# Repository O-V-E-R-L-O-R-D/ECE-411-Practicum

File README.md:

# ECE-411-Practicum Project

## Color Sensor State Diagram

## Bootload and Programming
**Library for Bootload Raw Chip:** https://github.com/MCUdude/
MiniCore

**1.) Add "https://mcudude.github.io/MiniCore/package_MCUdude_MiniCore_index.json" to Arduino IDE's "Additional boards manager URL's"**

---
**2.) Open example project "AruinoISP"**

---
**3.) Program Arduino Uno for programming by clicking "Upload button" with the Aruino Uno board selected. Also in the "Tools" tab select "ArduinoISP" for programmer** 

---
**4.) Make connections from Aruduino Uno to PCB. On PCB, move bottem left switch to Program Mode (PRGM) by sliding the switch to the left**

| Arduino Uno |->| PCB |
|-------------|--|-----|
|5V           |->|VCC  | 
|GND          |->|GND  |
|13           |->|CLK  |
|12           |->|MISO |
|11           |->|MOSI |
|10           |->|Reset|

---
**5.) Bootload ATmega328 by opening "Tools tab and clicking "Burn Bootloader" after changing the settings to the ones seen below.**  
Board: "ATmega328"
BOD: 2.7V  
Clock: "External 8MHz"  
EEPROM: "EEPROM not retained"  (Not Necessary, For Clearing Color Calibration data)  
Variant: "328P/32PA"  
Programmer: "Arduino as ISP"  

---
**6.) Switch to RGB_Sensor_Project.ino ("ECE-411-Practicum/RGB_sensor_project/RGB_sensor_project.ino"). Open Tools tab and make sure "Programmer" is set to "Arduino as ISP".With the ATmega328 board selected, open the "Sketch" tab and click "Upload Using Programmer"**

---
**7.) Unplug Programming connectings to PCB and flip the bottom right switch on the PCB to "NORM" mode. Make sure the PCB is getting power from the batter to the PCB. If this is the firt time programming the device the OLED should show that it's entering calibration mode.**  

**NOTE:** After first bootload you don't need to do it again for that chip. If you want to upload a new Schetch to the chip you only need to flip bottem left switch to PRGM, make the right programming connections, and then go straight to step 6.

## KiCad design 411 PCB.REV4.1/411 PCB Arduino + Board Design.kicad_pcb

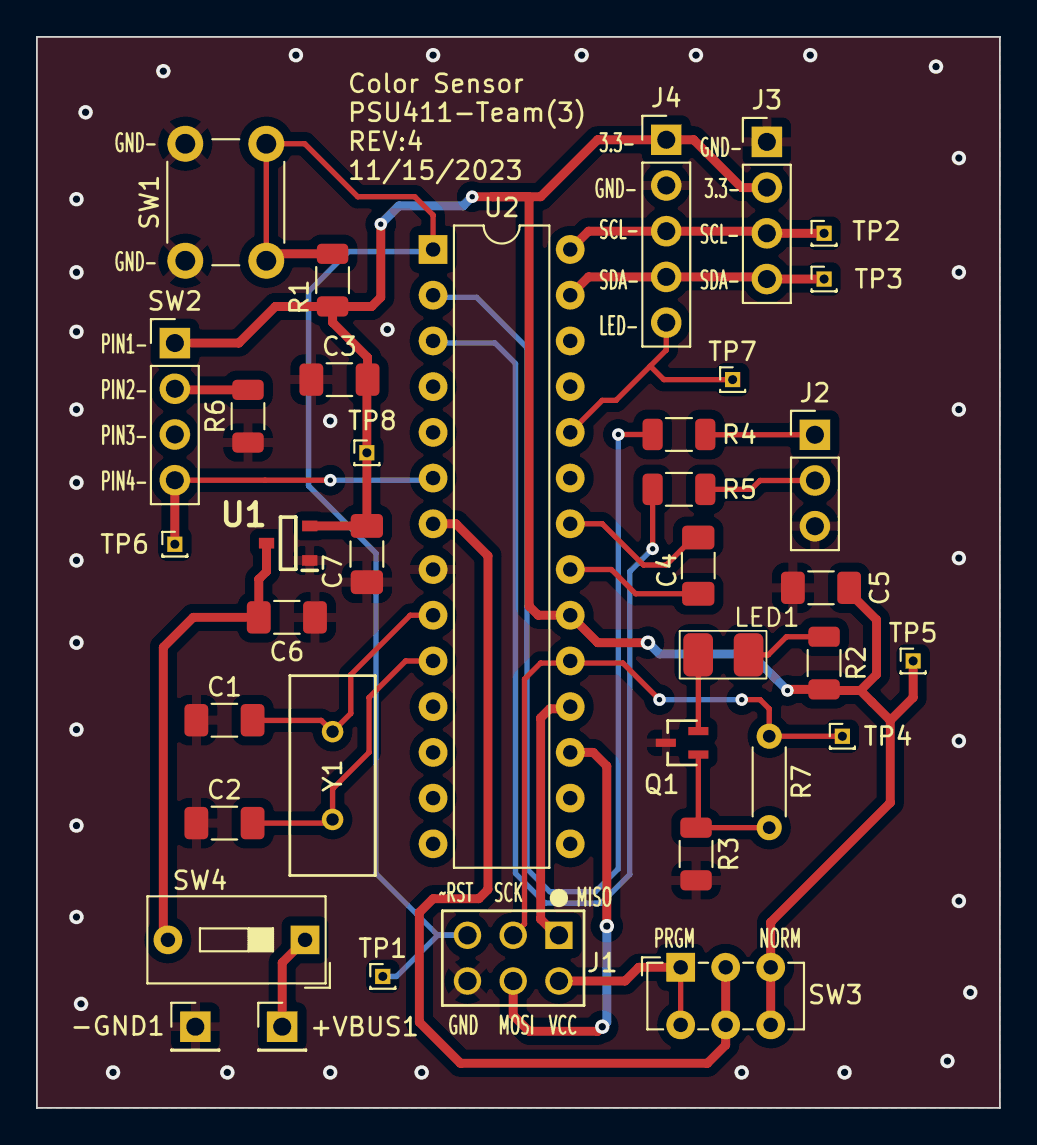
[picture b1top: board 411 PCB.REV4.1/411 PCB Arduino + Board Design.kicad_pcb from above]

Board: 2 copper layers, 53.5 x 59.5 mm, 37 parts (0 on the bottom side), 26 nets.

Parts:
+VBUS1: Conn_01x01_Pin; PinHeader_1x01_P2.54mm_Vertical
-GND1: Conn_01x01_Pin; PinHeader_1x01_P2.54mm_Vertical
C1, C2: 30p; C_1206_3216Metric_Pad1.33x1.80mm_HandSolder
C3, C4, C5: 100n; C_1206_3216Metric_Pad1.33x1.80mm_HandSolder
C6, C7: 1uF; C_1206_3216Metric_Pad1.33x1.80mm_HandSolder
J1: ICSP CONN; CONN_PH2-06-UA_ADM
J2: PinHeader_1x03_P2.54mm_Vertical
J3: Conn_01x04; PinHeader_1x04_P2.54mm_Vertical
J4: Conn_01x05_Pin; PinHeader_1x05_P2.54mm_Vertical
LED1: Blue LED (100mA Max); LTST-B680
Q1: Q_NMOS_GDS; SOIC_D8LW-13_DIO
R1, R3, R6: 10k; R_1206_3216Metric
R2, R4, R5: 1k; R_1206_3216Metric
R7: 0 Ohm; R_Axial_DIN0204_L3.6mm_D1.6mm_P5.08mm_Horizontal
SW1: SW_SPST; SW_PUSH_6mm
SW2: SW_MEC_5E; PinHeader_1x04_P2.54mm_Vertical
SW3: SW_SPDT; SW_E-Switch_EG1271_SPDT_123
SW4: SW_DPST_x2; SW_DIP_SPSTx01_Slide_9.78x4.72mm_W7.62mm_P2.54mm
TP1, TP2, TP3, TP4, TP5, TP6, TP7, TP8: TestPoint; PinHeader_1x01_P1.00mm_Vertical
U1: SOT96P240X120-3N
U2: ATmega328P-P; DIP-28_W7.62mm
Y1: 8 MHz; ATS08A-E_CTS

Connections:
+3.3V: C3.2, C5.2, C7.1, J3.2, J4.1, R1.1, R2.1, SW2.1, SW3.3 (C), TP5.1, TP8.1, U1.2 (VOUT), U2.20 (AVCC)
+5V: J1.2 (VCC), SW3.1 (A)
/LED_EN: J4.5, TP7.1, U2.24 ((ADC1)PC1)
/SDA+: J3.4, J4.4, TP3.1, U2.27 (SDA+)
/SDA-: J3.3, J4.3, TP2.1, U2.28 (SDA-)
GND: -GND1.1, C1.1, C2.1, C3.1, C5.1, C6.2, C7.2, J1.6 (GND), J2.3, J3.1, J4.2, Q1.3 (S), R3.2, R6.1, SW1.1 (A), U1.1 (GND), U2.8 (GND)
unnamed: +VBUS1.1, SW4.1 (A)
unnamed: C4.2, U2.22 (GND)
unnamed: J1.1 (MISO), U2.18 ((MISO)PB4)
unnamed: J1.4 (MOSI), U2.17 ((MOSI)PB3)
unnamed: J1.3 (SCK), R7.2, TP4.1, U2.19 ((SCK)PB5)
unnamed: J1.5 (~RST), R1.2, SW1.2 (B), TP1.1, U2.1 (~RESET/PC6)
unnamed: J2.1, R4.2
unnamed: J2.2, R5.2
unnamed: LED1.2 (A), R2.2
unnamed: LED1.1 (K), Q1.2 (D)
unnamed: Q1.1 (G), R3.1, R7.1
unnamed: R6.2, SW2.2
unnamed: SW2.4 (A), TP6.1, U2.6 ((T0)PD4)
unnamed: C6.1, SW4.2 (B), U1.3 (VIN)
unnamed: R4.1, U2.2 ((RXD)PD0)
unnamed: R5.1, U2.3 ((TXD)PD1)
unnamed: C4.1, U2.21 (AREF)
unnamed: C1.2, U2.9 (XTAL+), Y1.2
unnamed: C2.2, U2.10 (XTAL-), Y1.1
VCC: SW3.2 (B), U2.7 (VCC)

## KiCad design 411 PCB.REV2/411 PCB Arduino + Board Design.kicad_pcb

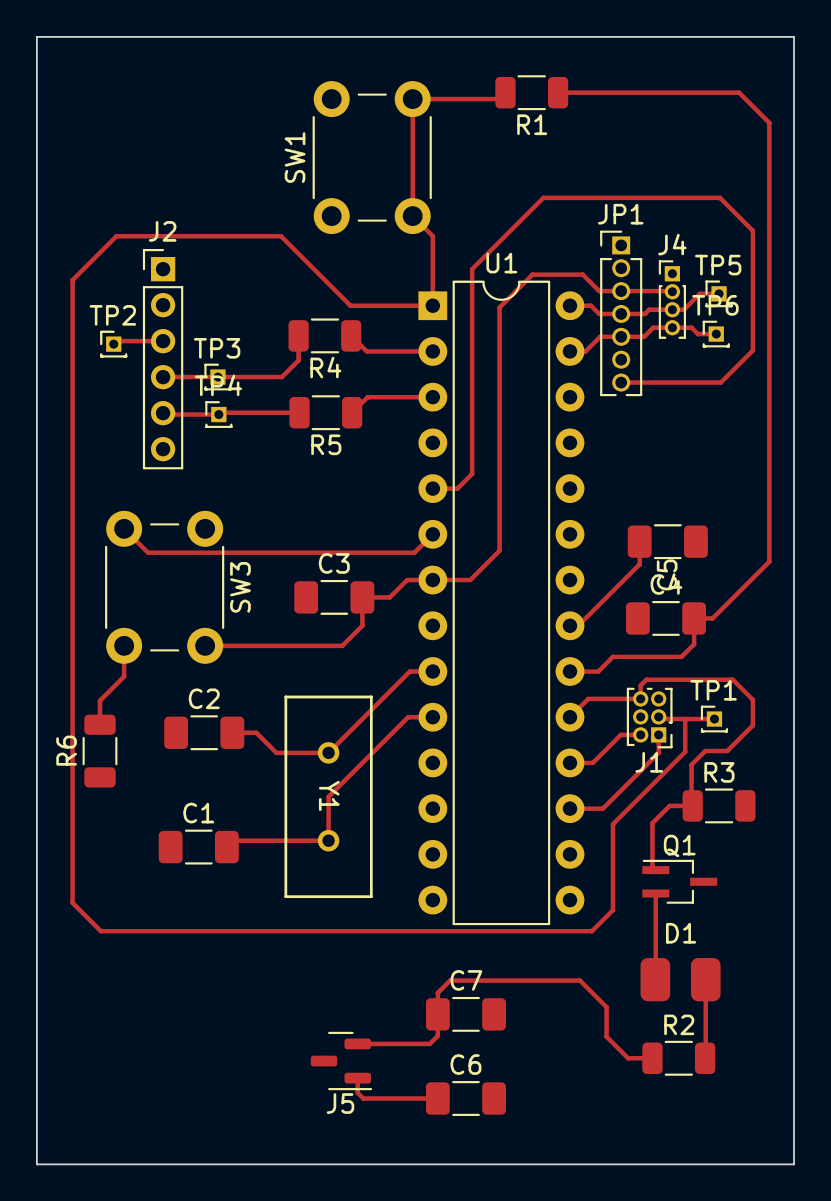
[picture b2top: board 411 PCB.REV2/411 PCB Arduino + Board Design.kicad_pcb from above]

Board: 2 copper layers, 42.1 x 62.6 mm, 30 parts (0 on the bottom side), 22 nets.

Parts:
C1, C2: 10p; C_1206_3216Metric_Pad1.33x1.80mm_HandSolder
C3, C4, C5: 100n; C_1206_3216Metric_Pad1.33x1.80mm_HandSolder
C6, C7: 1uF; C_1206_3216Metric_Pad1.33x1.80mm_HandSolder
D1: LED (100mA Max); LED_0805_2012Metric_Pad1.15x1.40mm_HandSolder
J1: ICSP CONN; PinHeader_2x03_P1.00mm_Vertical
J2: Conn_01x06_MountingPin; PinHeader_1x06_P2.00mm_Vertical
J4: Conn_01x04; PinHeader_1x04_P1.00mm_Vertical
J5: SOT-23
JP1: HEADER-1X770MIL; PinHeader_1x07_P1.27mm_Vertical
Q1: Q_NMOS_GDS; SOT-323_SC-70_Handsoldering
R1, R3, R6: 10k; R_1206_3216Metric
R2, R4, R5: 1k; R_1206_3216Metric
SW1: SW_SPST; SW_PUSH_6mm
SW3: SW_MEC_5E; SW_PUSH_6mm
TP1, TP2, TP3, TP4, TP5, TP6: TestPoint; PinHeader_1x01_P1.00mm_Vertical
U1: ATmega328P-P; DIP-28_W7.62mm
Y1: 8 MHz; ATS08A-E_CTS

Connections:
+3.3V: C3.2, C4.2, C7.1, J4.2, J5.2 (VOUT), JP1.3, R1.1, R2.1, SW3.1, U1.7 (VCC), U1.20 (AVCC)
+VDC: C6.1, J5.1 (VIN)
/LED_EN: JP1.7, U1.5 ((INT1)PD3)
/SCL_3.3V: J4.3, JP1.4, TP5.1, U1.28 ((ADC5/SCL)PC5)
/SDA_3.3V: J4.4, JP1.5, TP6.1, U1.27 ((ADC4/SDA)PC4)
GND: C1.1, C2.1, C3.1, C4.1, C5.1, C6.2, C7.2, J1.6 (GND), J2.1, J4.1, J5.3 (GND), JP1.2, Q1.3 (S), R3.2, R6.1, SW1.1 (A), U1.8 (GND), U1.22 (GND)
unnamed: D1.2 (A), R2.2
unnamed: D1.1 (K), Q1.2 (D)
unnamed: J1.1 (MISO), U1.18 ((MISO)PB4)
unnamed: J1.4 (MOSI), U1.17 ((MOSI)PB3)
unnamed: J1.3 (SCK), Q1.1 (G), R3.1, U1.19 ((SCK)PB5)
unnamed: J1.5 (~RST), R1.2, SW1.2 (B), TP1.1, U1.1 (~RESET/PC6)
unnamed: J2.3, TP2.1
unnamed: J2.4, R4.2, TP3.1
unnamed: J2.5, R5.2, TP4.1
unnamed: R6.2, SW3.2
unnamed: SW3.4 (A), U1.6 ((T0)PD4)
unnamed: R4.1, U1.2 ((RXD)PD0)
unnamed: R5.1, U1.3 ((TXD)PD1)
unnamed: C5.2, U1.21 (AREF)
unnamed: C2.2, U1.9 (XTAL1/PB6), Y1.1
unnamed: C1.2, U1.10 (XTAL2/PB7), Y1.2

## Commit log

2023-10-28 Create RGB_sensor_project.ino
    Arduino projector, getting basics of the color sensor and display working (together).
2023-10-28 Create RGB_sensor_project.ino (#1)
    Arduino projector, getting basics of the color sensor and display working (together).
2023-11-02 Create Link To Demo Video on Youtube
2023-11-02 Create Team Gratt
2023-11-03 Rename Jacob_code.ino to Project_sensor_code.ino
2023-11-06 Updated Folder Layout
    Newest PCB update
2023-11-06 Latest Schematic and PCB footprints
    Update-
2023-11-08 Adding first version of Bill Of Materials.
2023-11-08 Updated PCB Layout
2023-11-08 Updated bill of materials
2023-11-09 Create Color reader FD
2023-11-09 Create fd
2023-11-09 added lide switch
2023-11-09 Updated values and descriptions on Schematic
    Changed the capacitor values for the 8MHz clock from 20pF to 10pF. Added the Max current consumption of the color sensor, display, LED, and ATmega328P-PN. Also added the Max Current output for the Vo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
2023-11-10 New rev
2023-11-10 New Schematic for Rev 3 and updated BOM
2023-11-10 Removed RGB LED code and cleaned up code
2023-11-11 added LED connection for RGB Sensor
2023-11-11 starting to incorporate EEPROM
2023-11-11 Added EEPROM code and changed the pins for button and RGB Sensors LED. Also changed how the chip goes into calibration mode
2023-11-11 pins that work
2023-11-12 Fixed debounce error and added more test points to schematic
2023-11-12 EEPROM, Debounce, more testpoints (#2)
    * Create RGB_sensor_project.ino
    Arduino projector, getting basics of the color sensor and display working (together).
    * Removed RGB LED code and cleaned up code
    * added LED connection for RGB Sensor
    * starting to incorporate EEPROM
    * Added EEPROM code and changed the pins for button and RGB Sensors LED. Also changed how the chip goes into calibration mode
2023-11-13 Rev4 Fixed Footprint and Schematic Layout a bit.
    Monday 11/13/2023 Will do the PCB final routing
2023-11-13 411 PCB Rev4+ Updated and Routed Layout
    This is the pre submission board. Before Ben check
2023-11-14 OSH Park example
2023-11-15 PCB Layout REV 4
    Updated Schematic and Layout (Added power switches, fixed Atmega pin out schematic, changed pin outputs on color sensor, added 3.3V to 5V throw select switch)
2023-11-15 updated capacitators for crystal to 40pF
2023-11-15 43pF caps were the closest values of Digikey
2023-11-15 update BOM and real capacitor value for crystal
2023-11-16 OSH Park
2023-11-16 schematic
2023-11-16 pdf for pcb
2023-11-16 not the pdf i wanted to get
2023-11-16 Updated Board + PCB purchase receipt
    Yes
2023-11-16 Updated PCB and Loaded Receipt Board Purchase
2023-11-16 Uploaded Final Schematic and Layout PDF
2023-11-16 Final Updates during purchase
2023-11-27 mock up models
2023-11-28 more pictures
2023-11-28 Hello :) on turn on
    I added a Hello message when you turn on the device so you know it's working. Also fixed color sensor not detected error displaying correctly on OLED display. OLED display shouldn't say if it is work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
2023-11-29 Added state machine diagram to ReadMe
2023-11-29 Fixed AVCC and Big Button pinout on schamatic
    The AVCC should be connected to VCC and not 3.3V because when it's powered by 5V the AVCC pin would output 5V towards the Voltage regulator. The SW2 (big button) had ground on the wrong pin (floating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
2023-11-29 removed extra connection to 3.3V for no reason on AVCC line
2023-11-29 Removed C3 from BOM (Rev 4.1)
2023-11-29 Lowered debounce delay time and long press time
2023-11-29 Added programming and bootloading instruction to the ReadMe
2023-11-30 cleaned up ReadMe slightly
2023-12-04 Pics of Version 2.5
    updated lens with cap
2023-12-06 Add hello message after finishing calibration
2023-12-07 Fixed display bug. Forgot to add "setCursor"."
2023-12-07 Added switch/flag for serial debug code
2023-12-07 verstion4.0
2023-12-07 Increase the amount of time the light is on. This fixes the variance between measurements of the same color.
